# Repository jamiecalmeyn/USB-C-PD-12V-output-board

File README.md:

# USB-C PD 12V output board
Powered by the IP2721_MAX12
## PCB

Upgrade your legacy gear with modern USB-C power. This compact board delivers a 12V output using the IP2721_MAX12 USB-C Power Delivery controller.

Whether you're retrofitting old tech or building something new, this board offers a simple, reliable way to tap into USB-C PD at 12V. It uses the HRO_TYPE-C-31-M-17 USB connector.
It should be able to handle 1.5A of current based on PCB track width.

*Board tested with 1.5A of current*

*Ripple under a 1.5A load, ripple can vary based on the USB-C charger. Test conducted with the **65W USB-C GaN iFixit Fast Charger***
## IP2721_MAX12

⚠️ Important: Use the Correct Chip

Be sure to use the **IP2721_MAX12** chip.

Using the standard **IP2721** (without the _MAX12 suffix) will result in 20V output, which could damage 12V devices. Double-check your part number!
Do note that the 12V is an optional voltage output in the USB-C PD standard, not every charger has a 12V output mode. 
## Schematic

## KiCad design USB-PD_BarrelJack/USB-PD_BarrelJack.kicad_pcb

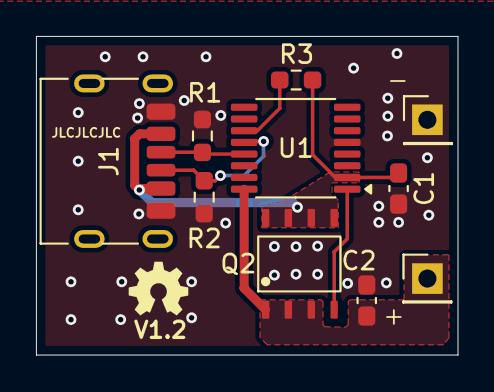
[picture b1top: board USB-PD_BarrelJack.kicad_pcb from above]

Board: 2 copper layers, 23.4 x 17.7 mm, 10 parts (0 on the bottom side), 7 nets.

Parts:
C1: 1u; C_0603_1608Metric_Pad1.08x0.95mm_HandSolder
C2: 10u; C_0603_1608Metric_Pad1.08x0.95mm_HandSolder
J1: USB_C_Receptacle_USB2.0_14P; USB_C_Receptacle_HRO_TYPE-C-31-M-17
J2: Vout; PinHeader_1x01_P2.54mm_Vertical
J3: GND; PinHeader_1x01_P2.54mm_Vertical
Q2: DMN3010LSS
R1, R2: 5.1k; R_0603_1608Metric_Pad0.98x0.95mm_HandSolder
R3: 100k; R_0603_1608Metric_Pad0.98x0.95mm_HandSolder
U1: IP2721; TSSOP-16_4.4x5mm_P0.65mm

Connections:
GND: C1.2, C2.2, J1.A12 (GND), J1.B12 (GND), J3.1, R1.2, R2.2, U1.5 (GND)
unnamed: J1.A5 (CC1), R1.1, U1.13 (CC1)
unnamed: J1.B5 (CC2), R2.1, U1.12 (CC2)
unnamed: Q2.4 (G), U1.1 (VBUSG)
unnamed: R3.1, U1.11 (SEL)
VBUS: C2.1, J2.1, Q2.1 (S), Q2.2 (S), Q2.3 (S), U1.16 (VBUS)
VCC: C1.1, J1.A9 (VBUS), J1.B9 (VBUS), Q2.5 (D), Q2.6 (D), Q2.7 (D), Q2.8 (D), R3.2, U1.2 (VIN)

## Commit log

2025-05-01 Initial push
2025-05-01 Update README.md
    Fixed oscilloscope image
2025-05-01 Update README.md
    typo
